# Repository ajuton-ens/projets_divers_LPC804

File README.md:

# Hexapode
 Ce projet consiste à mettre en marche un robot hexapode à l'aide d'une microcontrôleur LPC804. 
 Cet hexapode est constitué d'une base octogonale, et de six pattes situées à 45°, 90° et 135°, de façon symétrique par rapport à l'avant du robot. 
 Chacune des pattes est constituées de trois servomoteur [AX-12](https://emanual.robotis.com/docs/en/dxl/ax/ax-12a/) liés les uns aux autres, l'un d'eux étant accroché à la base octogonale, et un autre lié à un pied en plastique.

## Commande angulaire des servomoteurs
 Les servomoteurs se commandent à l'aide du [Dynamixel Protocol 1.0](https://emanual.robotis.com/docs/en/dxl/protocol1/). 
 Il consiste à envoyer une trame permettant d'identifier le moteur à commander, puis de lui demander d'exécuter diverses instructions, ce peut être de la lecture ou de l'écriture de données par exemple. 
 Du côté de la LPC804, l'émission des trames se fait à l'aide d'un périphérique UART par liaison série. 
 Pour imposer l'angle d'un servomoteur, il suffit alors d'envoyer une trame d'écriture à l'adresse 30 (goal position), suivi du LSB et du MSB de l'angle pour des valeurs entre 0 et 1023 (une règle de trois permet de retrouver l'angle réel). 
 Une fois la trame construite, elle est stockée dans un buffer circulaire puis chaque caractère est émis un à un à l'aide de l'interruption TXIDLE, qui déclenche une interruption lorsque la transmission n'est pas en cours. 
 Cette interruption est désactivée lorsque l'on a plus de donnée à émettre.

## Commande en position des pattes
 Les pattes sont pilotés en commandant la position cartésienne de l'extrémité des pieds.
 Pour cela, on dispose de plusieurs équations permettant de passer de la position désirée, aux trois angles à envoyer aux moteur de la patte.

## Trajectoire du robot
 Le robot suit une simple trajectoire rectiligne.
 La bibliothèque fournit était censé permettre une rotation, celle-ci n'a malheureusement jamais fonctionné.
 Afin d'effectuer cette trajectoire rectiligne, les pieds suivent une trajectoire circulaire.
 Par exemple pour aller tout droit, le pied central droit et les pieds extérieurs gauche vont suivre un cercle, les autres pieds vont suivre le même cercle avec un déphasage de 180°, ce qui permet au robot d'avancer.  

## Commande de la trajectoire par bluetooth
 Afin de piloter l'hexapode à distance, on utilise un périphérique permettant de convertir des données bluetooth en données lisible par liaison série, celles-ci sont émise via un smartphone et l'application [SENA BTerm Bluetooth Terminal](https://play.google.com/store/apps/details?id=com.sena.bterm&hl=fr&gl=US).
 Les données reçues permettent de faire les actions suivantes : 
  * 'Z' : Aller tout droit; 
  * 'Q' : Aller à gauche;
  * 'S' : Aller en arrière;
  * 'D' : Aller à droite;
  * 32 (espace) : S'arrêter; 

## Diagramme synoptique

###### Rendu
 à rendre sur https://github.com/ajuton-ens/projets_divers_LPC804

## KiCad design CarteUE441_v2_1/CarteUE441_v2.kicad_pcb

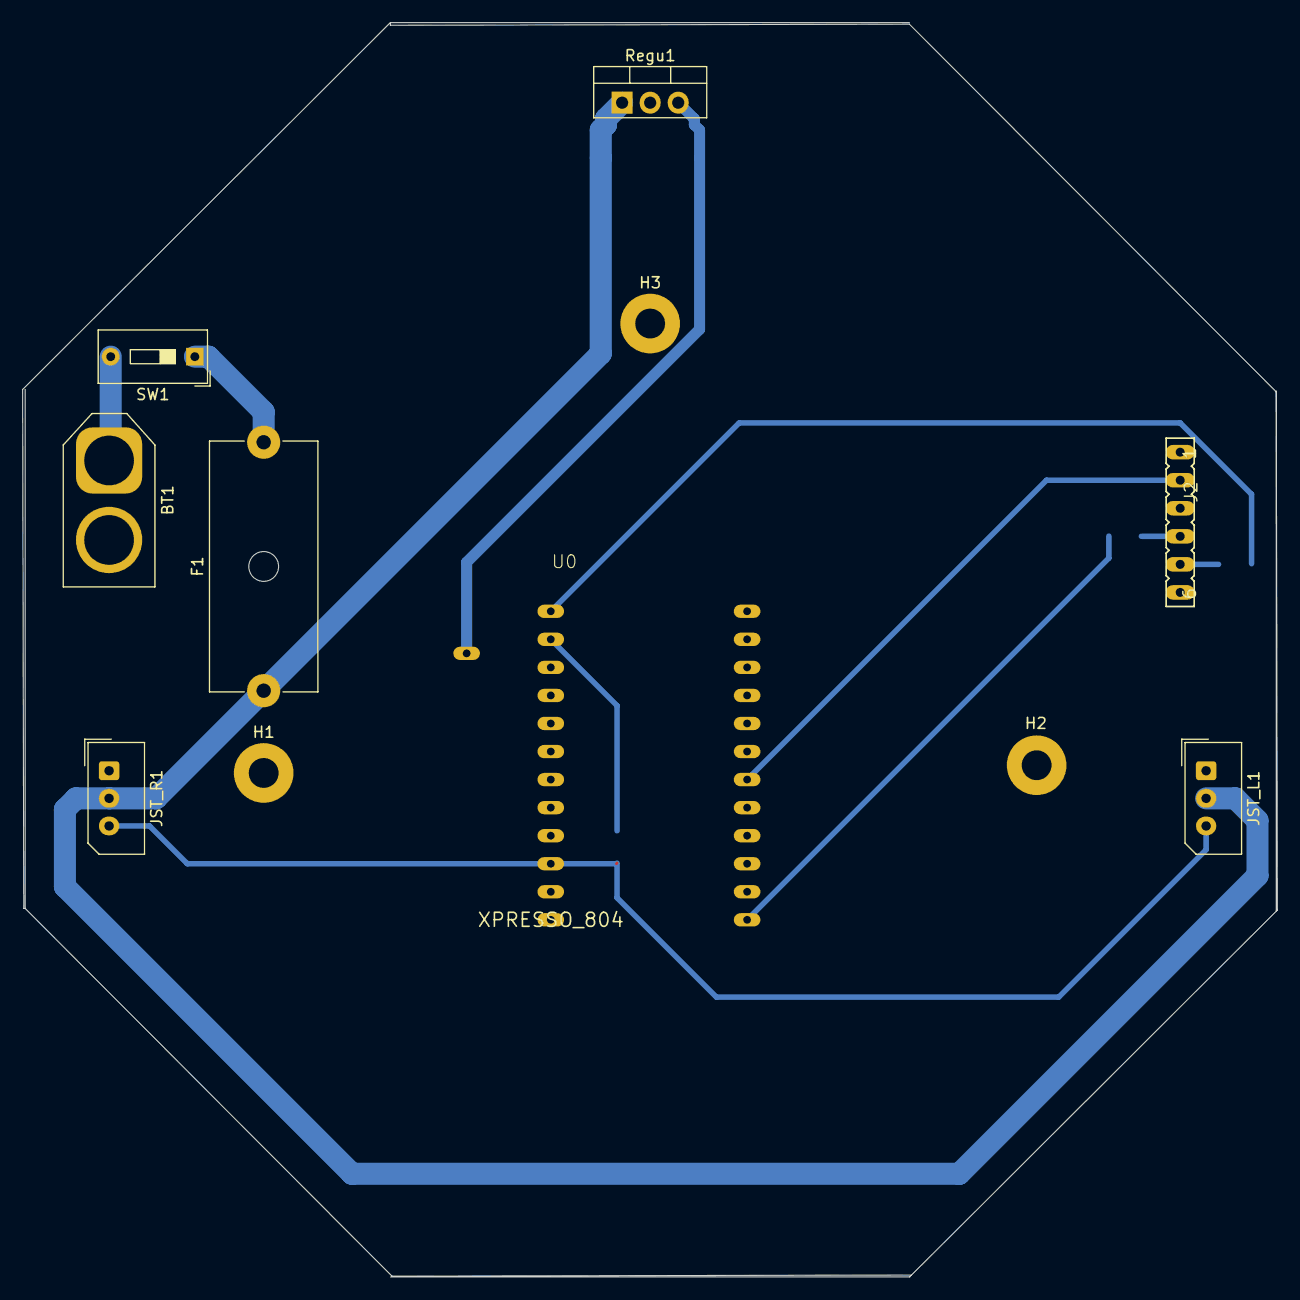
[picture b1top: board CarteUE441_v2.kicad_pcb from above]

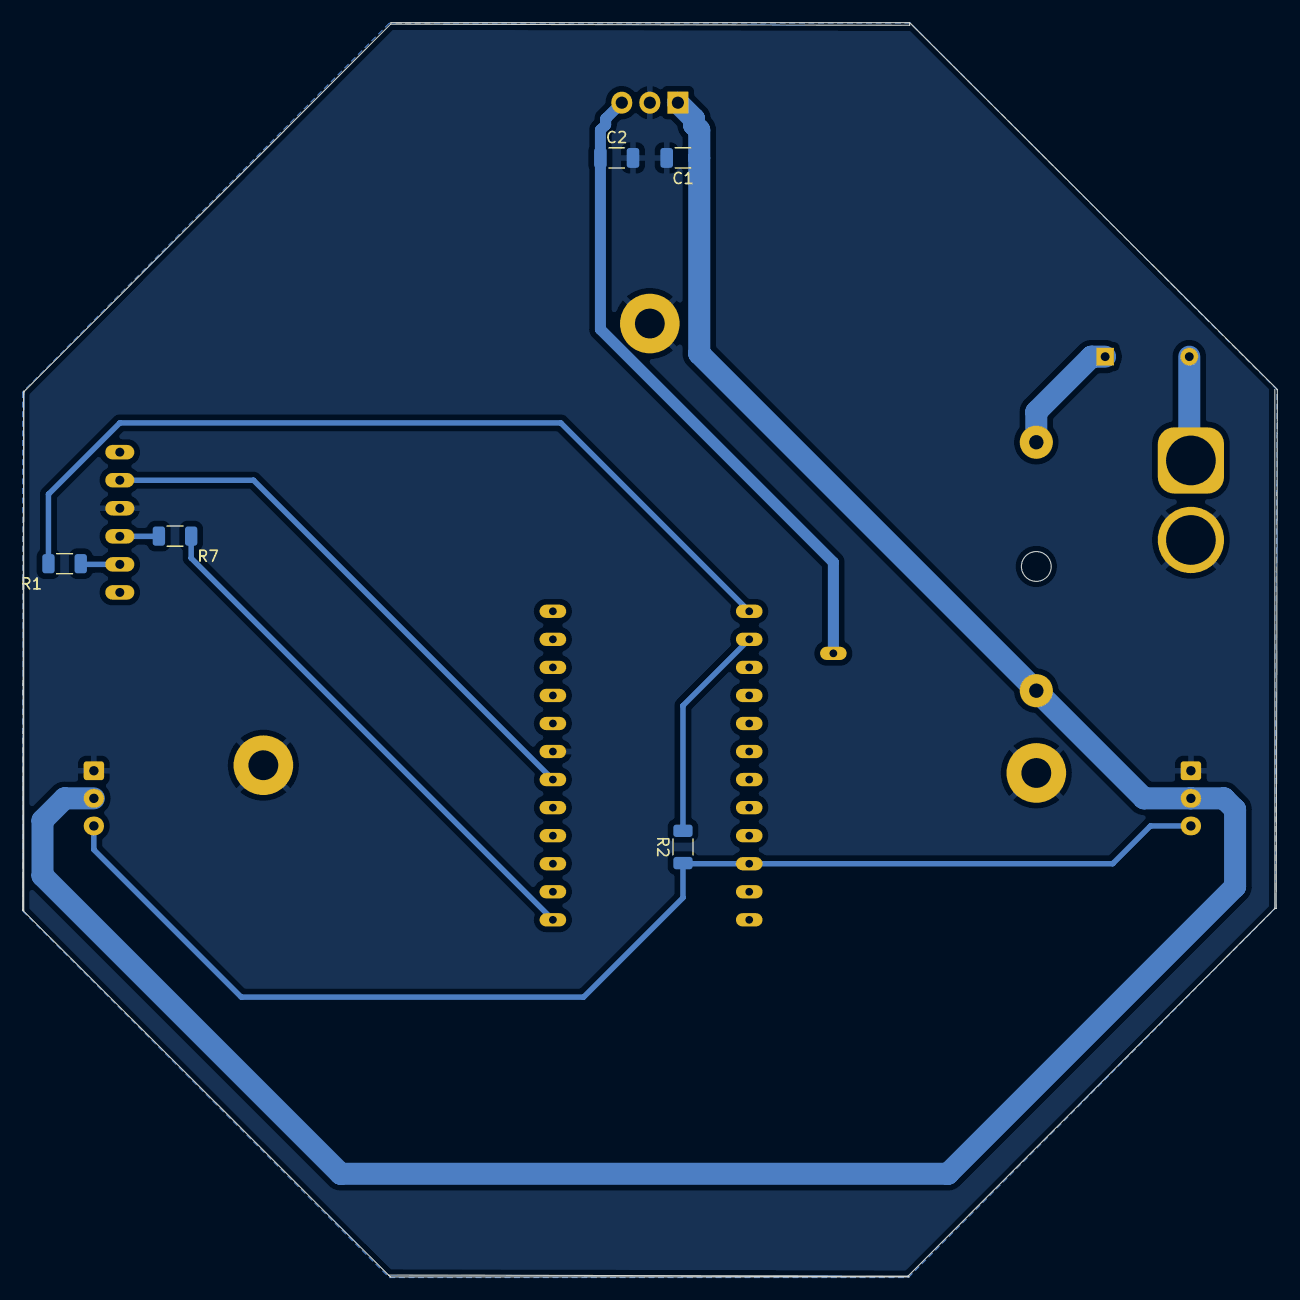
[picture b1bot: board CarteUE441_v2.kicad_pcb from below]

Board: 2 copper layers, 113.6 x 113.6 mm, 16 parts (5 on the bottom side), 12 nets.

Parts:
BT1: Battery; AMASS_XT60-F_1x02_P7.20mm_Vertical
C1: 330nF; C_1206_3216Metric
C2: 100nF; C_1206_3216Metric
F1: Fuse; Fuseholder_Cylinder-5x20mm_Schurter_0031_8201_Horizontal_Op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
H1, H2, H3: MountingHole_Pad; MountingHole_2.7mm_Pad
J2: SERIE; CON-LSTA_FE06
JST_L1: Conn_01x03_Male; Molex_SPOX_5267-03A_1x03_P2.50mm_Vertical
JST_R1: Conn_01x03_Male; Molex_SPOX_5267-03A_1x03_P2.50mm_Vertical
R1, R7: 560; R_1206_3216Metric
R2: 1kOhm; R_1206_3216Metric
Regu1: L7805; TO-220-3_Vertical
SW1: SW_SPST; SW_DIP_SPSTx01_Slide_9.78x4.72mm_W7.62mm_P2.54mm
U0: XPRESSO_804; LIB_ENS_AJ_V1_XPRESSO_804

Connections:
+12V: C1.1, F1.1, JST_L1.2, JST_R1.2, Regu1.1 (IN)
/Rx0: JST_L1.3, JST_R1.3, R2.1, U0.P$10 (P011_LED4)
/Tx0: R2.2, U0.P$2 (P016_SPICSW25X10)
/UART_RX1: J2.4, R7.2
/UART_TX1: J2.5, R1.1
/VCC_5V: C2.1, Regu1.3 (OUT), U0.5V_USB
/VDD: J2.2, U0.P$18 (VDD)
GND: BT1.2 (-), C1.2, C2.2, H1.1, H2.1, H3.1, J2.3, JST_L1.1, JST_R1.1, Regu1.2 (GND), U0.P$19 (GND)
unnamed: BT1.1 (+), SW1.2 (B)
unnamed: F1.2, SW1.1 (A)
unnamed: R1.2, U0.P$1 (P018)
unnamed: R7.1, U0.P$13 (P020)

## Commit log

2021-11-22 Rename README.txt to README.md
2021-12-12 Rx disabled
    RX functions disabled (useless as motor send nothing)
2021-12-13 It walks !
    Finally, le 17 sur 20 !!!
2021-12-13 Test fini
    Test en haute vitesse + haute amplitude terminés avec succès. La fonction de rotation fait n'importe quoi par contre.
2022-01-07 Modif bluetooth
    Ajout du second uart pour la commande par module bluetooth
2022-01-08 Images
2022-01-08 image
2022-01-08 Commentaires
2022-01-09 PCB carte électronique
